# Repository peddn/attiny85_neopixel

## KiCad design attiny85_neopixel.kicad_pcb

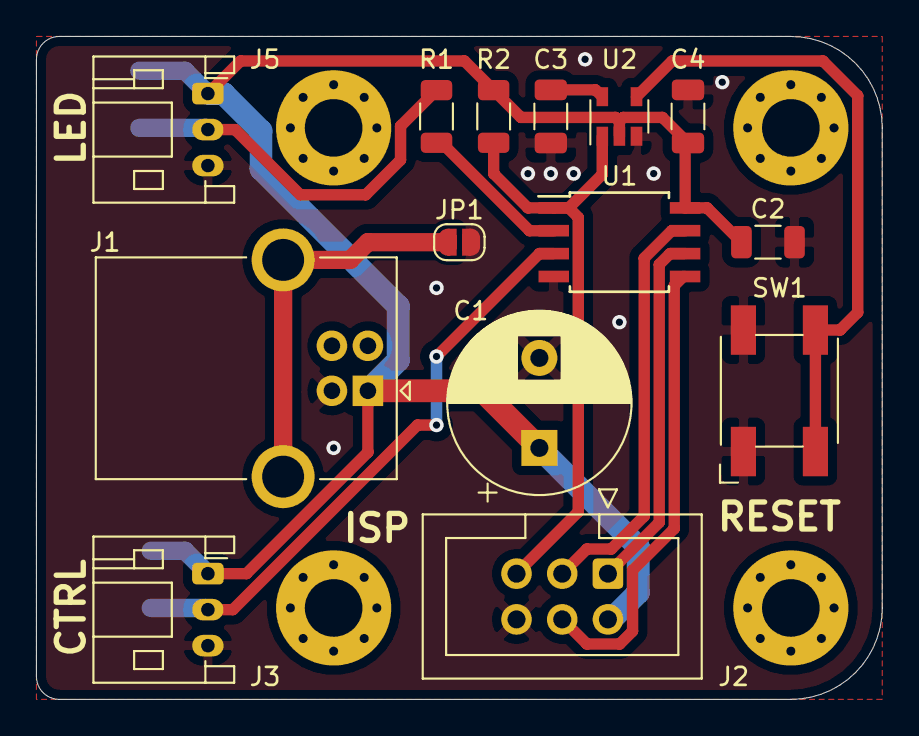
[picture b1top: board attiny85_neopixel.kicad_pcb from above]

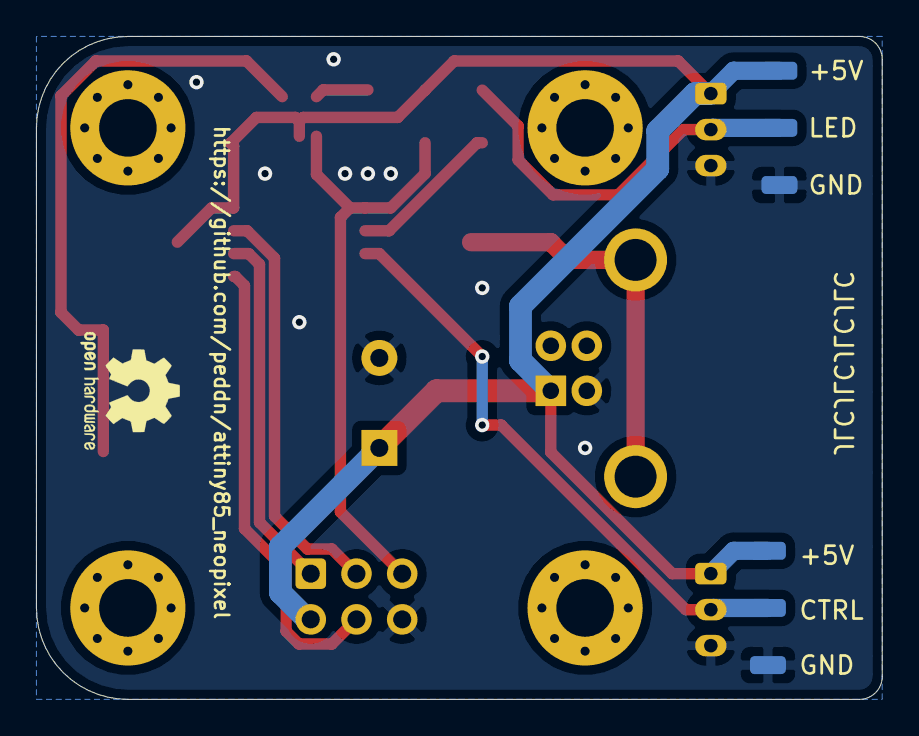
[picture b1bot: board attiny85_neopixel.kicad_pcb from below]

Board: 2 copper layers, 47.0 x 36.8 mm, 24 parts (6 on the bottom side), 12 nets.

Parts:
C1: 1000u; CP_Radial_D10.0mm_P5.00mm
C2: 0.1u; C_1206_3216Metric
C3, C4: 1u; C_1206_3216Metric
H1, H2, H3, H4: MountingHole; MountingHole_3.2mm_M3_Pad_Via
J1: USB_B; USB_B_OST_USB-B1HSxx_Horizontal
J2: Programming Connector; IDC-Header_2x03_P2.54mm_Vertical
J3: CONTROL Connector; JST_PH_S3B-PH-K_1x03_P2.00mm_Horizontal
J4, J6: Conn_5V; SolderWirePad_1x01_SMD_1x2mm
J5: LED Connector; JST_PH_S3B-PH-K_1x03_P2.00mm_Horizontal
J7: Conn_CONTROL; SolderWirePad_1x01_SMD_1x2mm
J8, J10: Conn_GND; SolderWirePad_1x01_SMD_1x2mm
J9: Conn_LED; SolderWirePad_1x01_SMD_1x2mm
JP1: Solder Jumper SHIELD; SolderJumper-2_P1.3mm_Open_RoundedPad1.0x1.5mm
R1: 470; R_1206_3216Metric
R2: 10k; R_1206_3216Metric
SW1: SW_TACTILE; SW_SPST_Omron_B3FS-100xP
U1: ATtiny85-20SU; SOIJ-8_5.3x5.3mm_P1.27mm
U2: TPS3840DL45DBVR; SOT-23-5

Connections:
+5V: C1.1, C2.1, C4.1, J1.1, J2.2, J3.1, J4.1, J5.1, J6.1, R2.1, U1.8, U2.2
/CONTROL: J3.2, J7.1, U1.3
/LED: J5.2, J9.1, R1.1
/MISO: J2.1, U1.6
/MOSI: J2.4, U1.5
/SCK: J2.3, U1.7
/~RESET: J2.5, R2.2, U1.1, U2.1
GND: C1.2, C2.2, C3.2, C4.2, J1.4, J2.6, J3.3, J5.3, J8.1, J10.1, JP1.2, SW1.1, SW1.2, U1.4, U2.3
unnamed: C3.1, U2.5
unnamed: J1.5, JP1.1
unnamed: R1.2, U1.2
unnamed: SW1.3, SW1.4, U2.4

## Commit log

2021-11-11 initial import
